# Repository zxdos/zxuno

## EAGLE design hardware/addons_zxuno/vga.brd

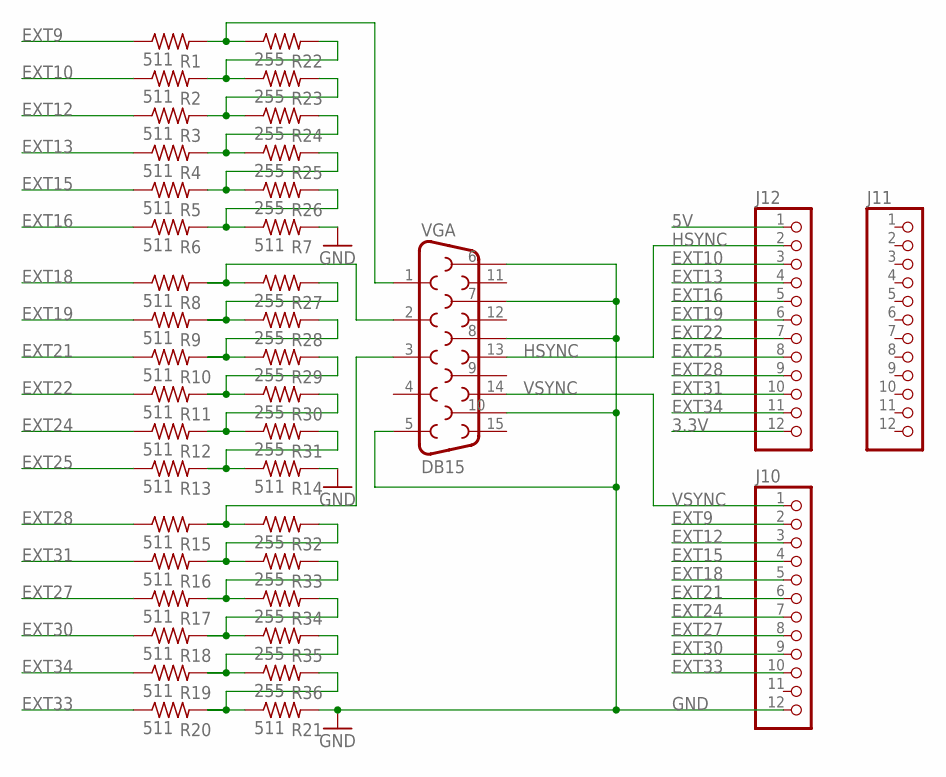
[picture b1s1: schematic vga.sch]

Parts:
J10, J11, J12: PINHD-1X12; 1X12
R1, R2, R3, R4, R5, R6, R7, R8, R9, R10, R11, R12, R13, R14, R15, R16, R17, R18, R19, R20, R21: 511; R0805
R22, R23, R24, R25, R26, R27, R28, R29, R30, R31, R32, R33, R34, R35, R36: 255; R0805
VGA: DB15

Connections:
3.3V: J12.12
5V: J12.1
EXT9: J10.2, R1.1
EXT10: J12.3, R2.1
EXT12: J10.3, R3.1
EXT13: J12.4, R4.1
EXT15: J10.4, R5.1
EXT16: J12.5, R6.1
EXT18: J10.5, R8.1
EXT19: J12.6, R9.1
EXT21: J10.6, R10.1
EXT22: J12.7, R11.1
EXT24: J10.7, R12.1
EXT25: J12.8, R13.1
EXT27: J10.8, R17.1
EXT28: J12.9, R15.1
EXT30: J10.9, R18.1
EXT31: J12.10, R16.1
EXT33: J10.10, R20.1
EXT34: J12.11, R19.1
GND: J10.12, R7.2, R14.2, R21.2, VGA.5, VGA.6, VGA.7, VGA.8, VGA.10
GREEN: R8.2, R27.1, VGA.2
HSYNC: J12.2, VGA.13
unnamed: R20.2, R21.1, R36.2
unnamed: R9.2, R27.2, R28.1
unnamed: R2.2, R22.2, R23.1
unnamed: R1.2, R22.1, VGA.1
unnamed: R12.2, R30.2, R31.1
unnamed: R6.2, R7.1, R26.2
unnamed: R3.2, R23.2, R24.1
unnamed: R4.2, R24.2, R25.1
unnamed: R5.2, R25.2, R26.1
unnamed: R11.2, R29.2, R30.1
unnamed: R13.2, R14.1, R31.2
unnamed: R10.2, R28.2, R29.1
unnamed: R15.2, R32.1, VGA.3
unnamed: R16.2, R32.2, R33.1
unnamed: R17.2, R33.2, R34.1
unnamed: R18.2, R34.2, R35.1
unnamed: R19.2, R35.2, R36.1
VSYNC: J10.1, VGA.14

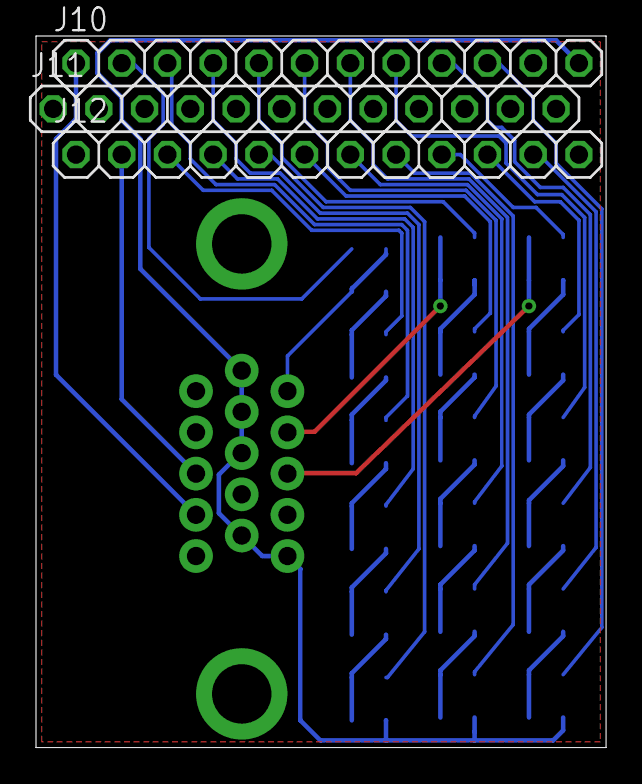
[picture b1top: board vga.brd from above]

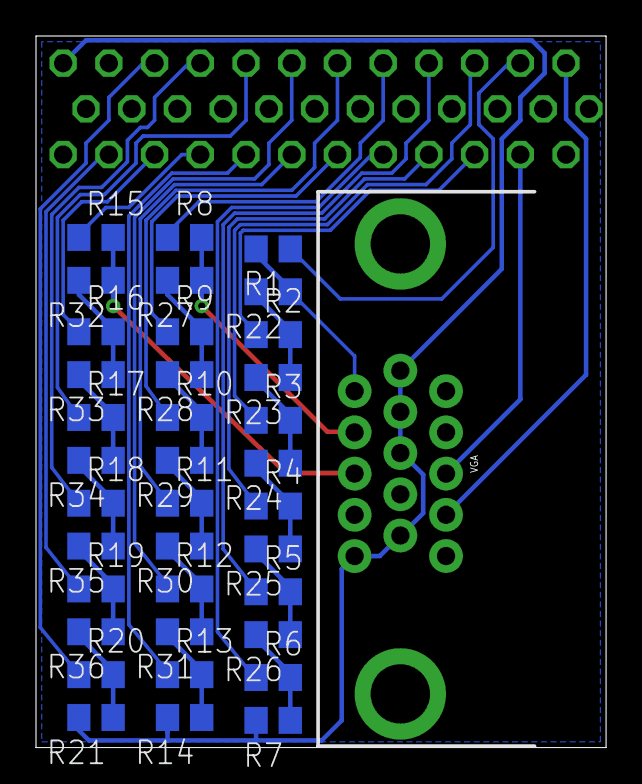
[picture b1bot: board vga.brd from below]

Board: 2 copper layers, 31.7 x 39.5 mm, 40 parts (37 on the bottom side), 39 nets.

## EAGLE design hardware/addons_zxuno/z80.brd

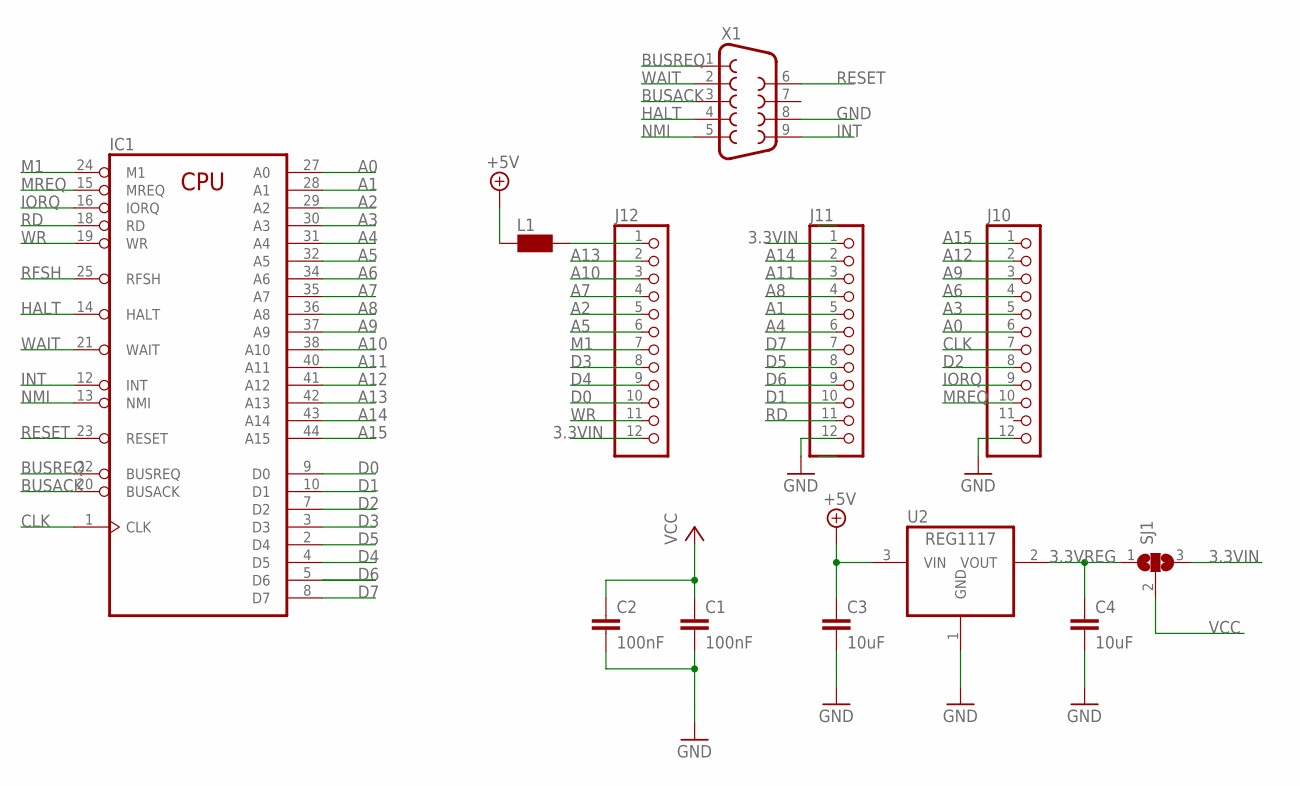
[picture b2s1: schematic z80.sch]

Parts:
C1, C2: 100nF; C0805K
C3, C4: 10uF; C0805K
IC1: Z80CPU-F; QFP-44
J10, J11, J12: PINHD-1X12; 1X12
L1: WE-CBF_0805; 0805
SJ1: SJ2W; SJ_2
U2: REG1117; SOT223
X1: F09D

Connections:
3.3VIN: J11.1, J12.12, SJ1.3
3.3VREG: C4.1, SJ1.1, U2.2 (VOUT)
+5V: C3.1, L1.2, U2.3 (VIN)
A0: IC1.27 (A0), J10.6
A1: IC1.28 (A1), J11.5
A2: IC1.29 (A2), J12.5
A3: IC1.30 (A3), J10.5
A4: IC1.31 (A4), J11.6
A5: IC1.32 (A5), J12.6
A6: IC1.34 (A6), J10.4
A7: IC1.35 (A7), J12.4
A8: IC1.36 (A8), J11.4
A9: IC1.37 (A9), J10.3
A10: IC1.38 (A10), J12.3
A11: IC1.40 (A11), J11.3
A12: IC1.41 (A12), J10.2
A13: IC1.42 (A13), J12.2
A14: IC1.43 (A14), J11.2
A15: IC1.44 (A15), J10.1
BUSACK: IC1.20 (BUSACK), X1.3
BUSREQ: IC1.22 (BUSREQ), X1.1
CLK: IC1.1 (CLK), J10.7
D0: IC1.9 (D0), J12.10
D1: IC1.10 (D1), J11.10
D2: IC1.7 (D2), J10.8
D3: IC1.3 (D3), J12.8
D4: IC1.4 (D5), J12.9
D5: IC1.2 (D4), J11.8
D6: IC1.5 (D6), J11.9
D7: IC1.8 (D7), J11.7
GND: C1.2, C2.2, C3.2, C4.2, IC1.26 (GND), J10.12, J11.12, U2.1 (GND), X1.8
HALT: IC1.14 (HALT), X1.4
INT: IC1.12 (INT), X1.9
IORQ: IC1.16 (IORQ), J10.9
M1: IC1.24 (M1), J12.7
MREQ: IC1.15 (MREQ), J10.10
unnamed: J12.1, L1.1
NMI: IC1.13 (NMI), X1.5
RD: IC1.18 (RD), J11.11
RESET: IC1.23 (RESET), X1.6
RFSH: IC1.25 (RFSH)
VCC: C1.1, C2.1, IC1.6 (VCC), SJ1.2
WAIT: IC1.21 (WAIT), X1.2
WR: IC1.19 (WR), J12.11

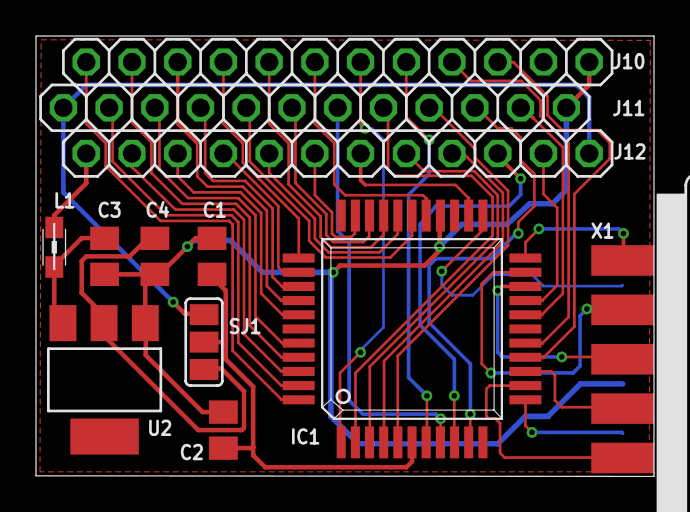
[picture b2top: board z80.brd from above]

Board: 2 copper layers, 34.3 x 24.5 mm, 12 parts (0 on the bottom side), 43 nets.

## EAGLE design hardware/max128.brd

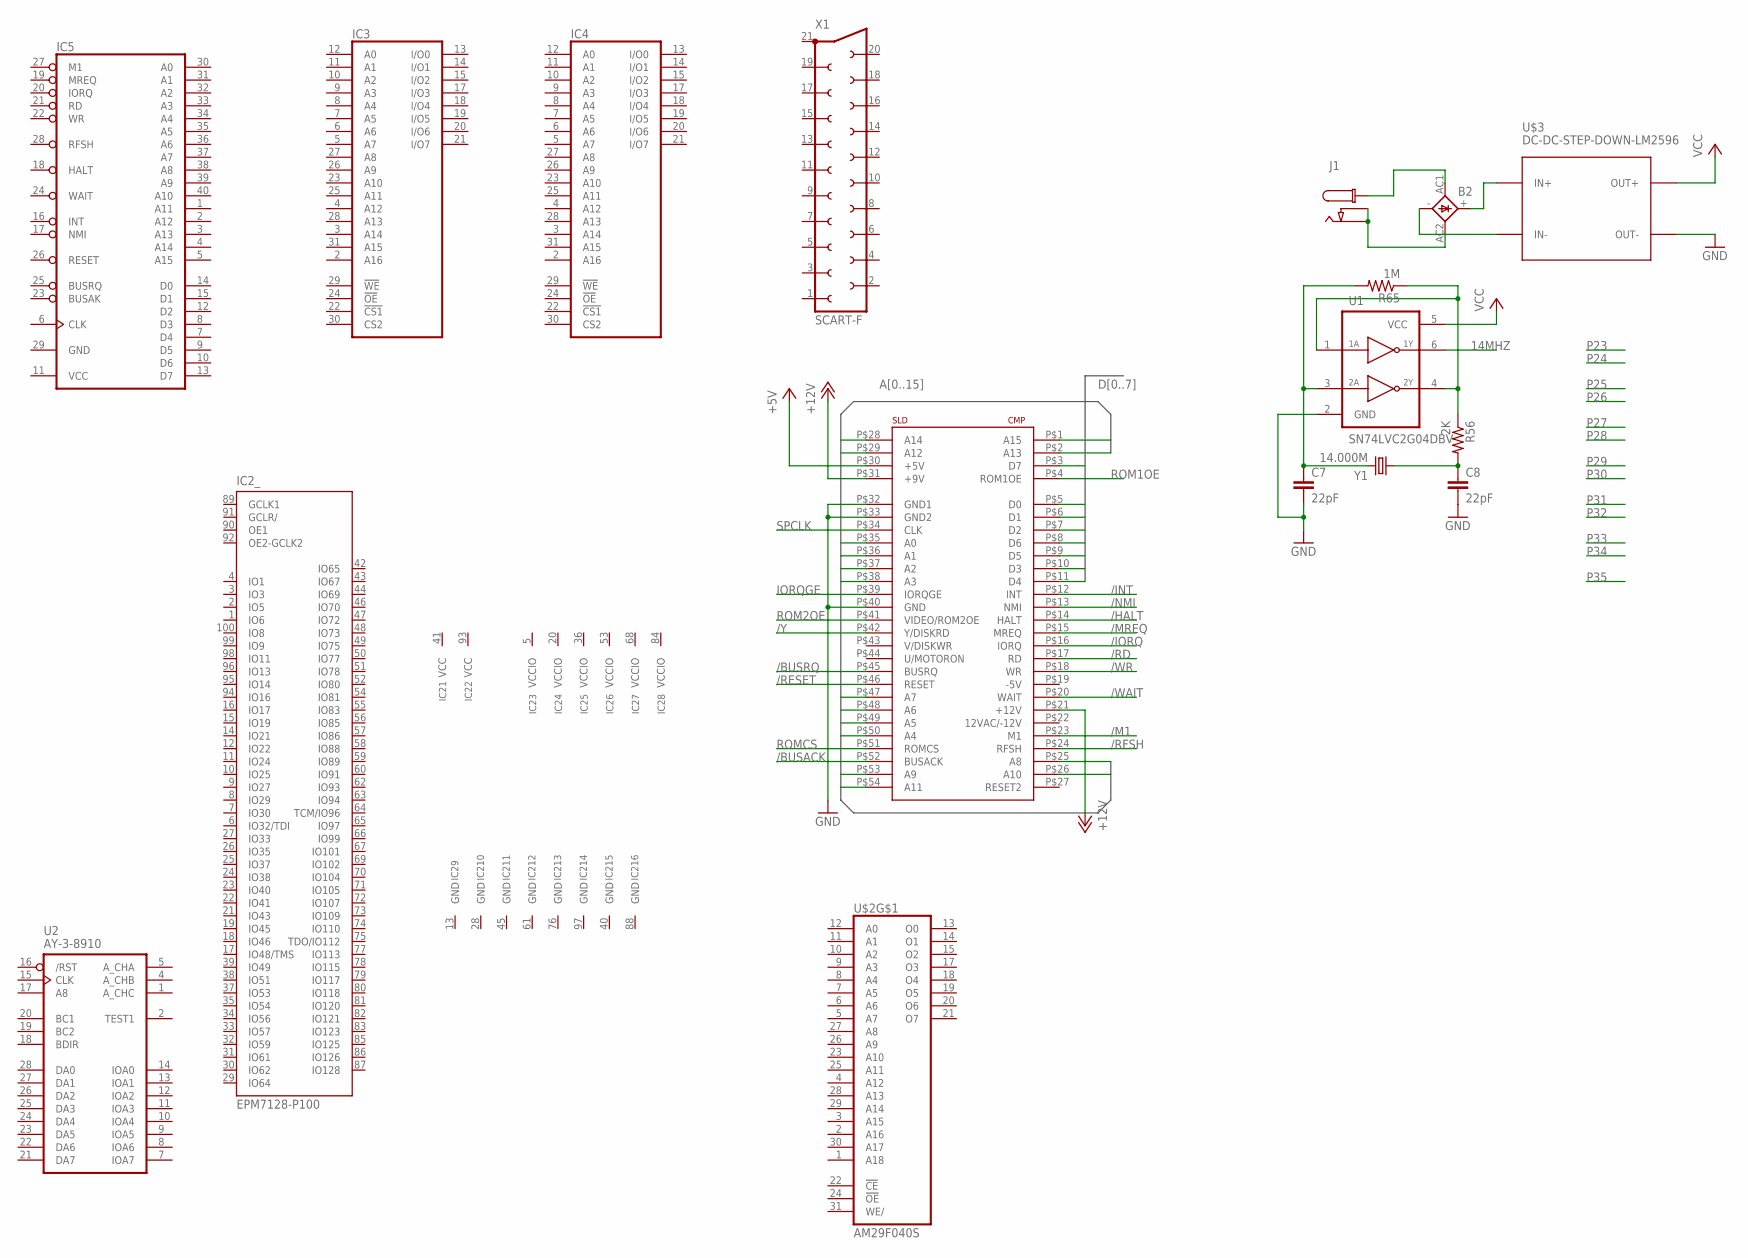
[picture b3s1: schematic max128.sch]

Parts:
B2: 1KAB
C7, C8: 22pF; C0805K
IC2: EPM7128-P100; PQFP100
IC3, IC4: LP621024CM; SOP32L
IC5: Z80CPU; DIL40
J1: CON_DC_M-DC_PTH2; DC_BARREL_JACK_PTH_2MM_2
R56: 2K; R0805
R65: 1M; R0805
U1: SN74LVC2G04DBV; SOT23-6
U2: AY-3-8910; DIL28-6
U$1: CONECTOR_EDGE_LADO_SPECTRUM; CONECTOR_LADO_SPECTRUM
U$2: AM29F040S; PLCC-SR32
U$3: DC-DC-STEP-DOWN-LM2596
X1: SCART-F
Y1: 14.000M; HC49/S

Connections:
14MHZ: U1.6 (1Y)
+5V: U$1.P$30 (+5V)
+12V: U$1.P$21 (+12V), U$1.P$31 (+9V)
/BUSACK: U$1.P$52 (BUSACK)
/BUSRQ: U$1.P$45 (BUSRQ)
/HALT: U$1.P$14 (HALT)
/INT: U$1.P$12 (INT)
/IORQ: U$1.P$16 (IORQ)
/M1: U$1.P$23 (M1)
/MREQ: U$1.P$15 (MREQ)
/NMI: U$1.P$13 (NMI)
/RD: U$1.P$17 (RD)
/RESET: U$1.P$46 (RESET)
/RFSH: U$1.P$24 (RFSH)
/WAIT: U$1.P$20 (WAIT)
/WR: U$1.P$18 (WR)
/Y: U$1.P$42 (Y/DISKRD)
A0: U$1.P$35 (A0)
A1: U$1.P$36 (A1)
A2: U$1.P$37 (A2)
A3: U$1.P$38 (A3)
A4: U$1.P$50 (A4)
A5: U$1.P$49 (A5)
A6: U$1.P$48 (A6)
A7: U$1.P$47 (A7)
A8: U$1.P$25 (A8)
A9: U$1.P$53 (A9)
A10: U$1.P$26 (A10)
A11: U$1.P$54 (A11)
A12: U$1.P$29 (A12)
A13: U$1.P$2 (A13)
A14: U$1.P$28 (A14)
A15: U$1.P$1 (A15)
D0: U$1.P$5 (D0)
D1: U$1.P$6 (D1)
D2: U$1.P$7 (D2)
D3: U$1.P$10 (D3)
D4: U$1.P$11 (D4)
D5: U$1.P$9 (D5)
D6: U$1.P$8 (D6)
D7: U$1.P$3 (D7)
GND: C7.2, C8.2, IC2.13 (GND), IC2.28 (GND), IC2.40 (GND), IC2.45 (GND), IC2.61 (GND), IC2.76 (GND), IC2.88 (GND), IC2.97 (GND), IC3.16 (GND), IC4.16 (GND), IC5.29 (GND), U1.2 (GND), U2.6 (GND), U$1.P$32 (GND1), U$1.P$33 (GND2), U$1.P$40 (GND), U$2.16 (GND), U$3.OUT-
IORQGE: U$1.P$39 (IORQGE)
unnamed: B2.AC1, J1.P1
unnamed: B2.AC2, J1.P2 (P3), J1.P3 (P2)
unnamed: B2.+, U$3.IN+
unnamed: B2.-, U$3.IN-
unnamed: C7.1, R65.2, U1.3 (2A), Y1.2
unnamed: R56.1, R65.1, U1.1 (1A), U1.4 (2Y)
unnamed: C8.1, R56.2, Y1.1
ROM1OE: U$1.P$4 (ROM1OE)
ROM2OE: U$1.P$41 (VIDEO/ROM2OE)
ROMCS: U$1.P$51 (ROMCS)
SPCLK: U$1.P$34 (CLK)
VCC: IC2.41 (VCC), IC2.93 (VCC), IC3.32 (VCC), IC4.32 (VCC), IC5.11 (VCC), U1.5 (VCC), U2.3 (VCC), U$2.32 (VCC), U$3.OUT+
VCCIO: IC2.5 (VCCIO), IC2.20 (VCCIO), IC2.36 (VCCIO), IC2.53 (VCCIO), IC2.68 (VCCIO), IC2.84 (VCCIO)

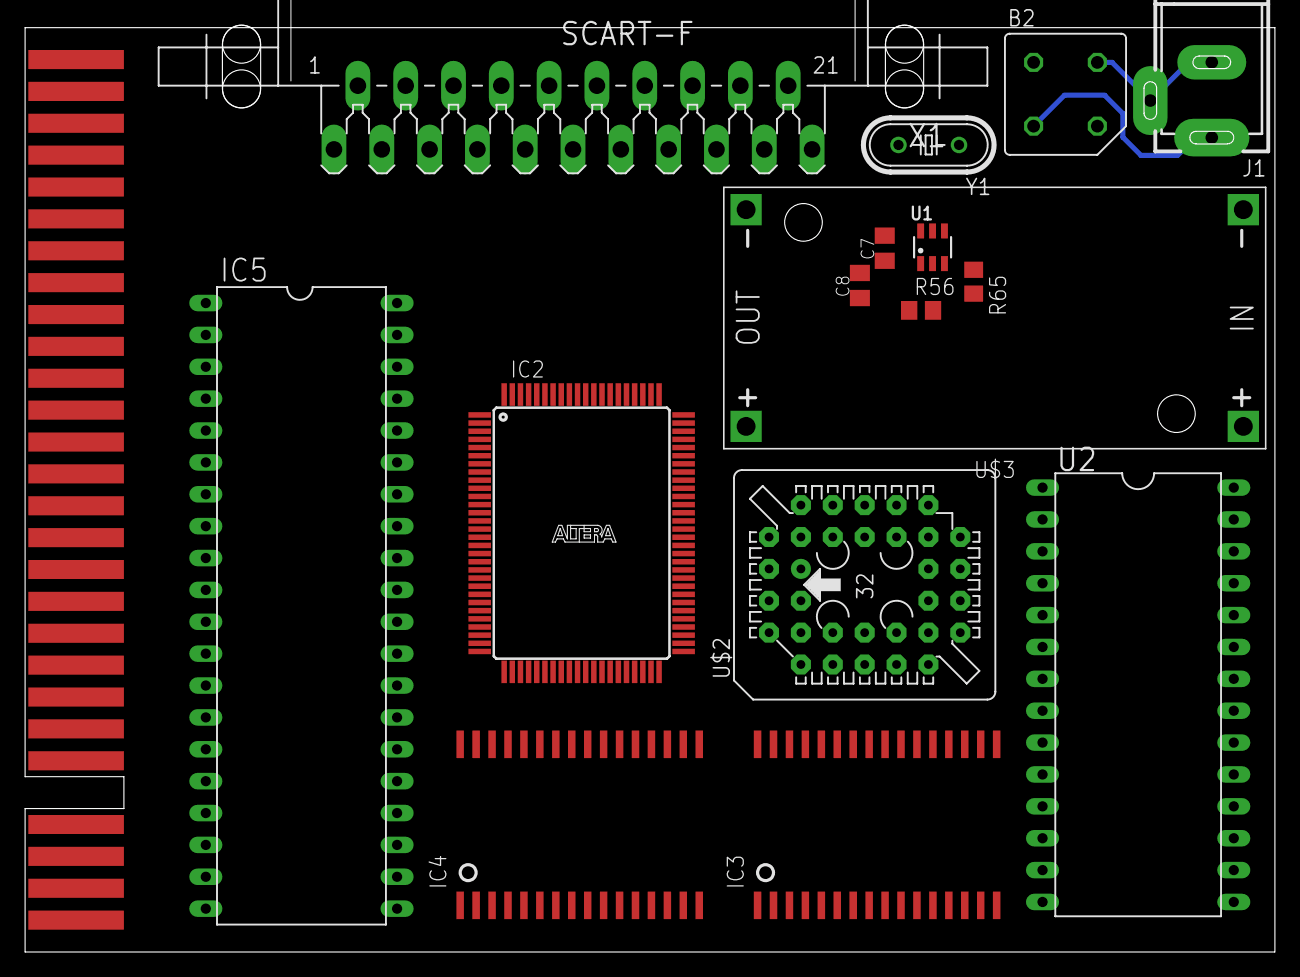
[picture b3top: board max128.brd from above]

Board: 2 copper layers, 99.6 x 73.7 mm, 17 parts (0 on the bottom side), 11 nets.

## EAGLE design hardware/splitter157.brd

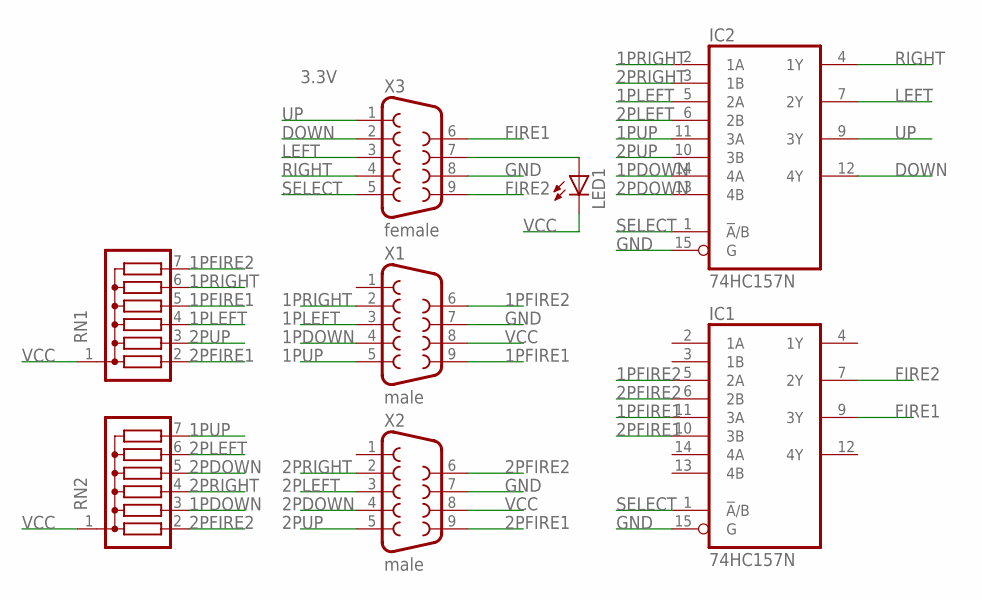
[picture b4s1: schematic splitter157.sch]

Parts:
IC1, IC2: 74HC157N; DIL16NUEVO
LED1: LED3MM
RN1, RN2: G06R; SIL7
X1, X2: male; F09D
X3: female; F09D

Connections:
1PDOWN: IC2.14 (4A), RN2.3, X1.4
1PFIRE1: IC1.11 (3A), RN1.5, X1.9
1PFIRE2: IC1.5 (2A), RN1.7, X1.6
1PLEFT: IC2.5 (2A), RN1.4, X1.3
1PRIGHT: IC2.2 (1A), RN1.6, X1.2
1PUP: IC2.11 (3A), RN2.7, X1.5
2PDOWN: IC2.13 (4B), RN2.5, X2.4
2PFIRE1: IC1.10 (3B), RN1.2, X2.9
2PFIRE2: IC1.6 (2B), RN2.2, X2.6
2PLEFT: IC2.6 (2B), RN2.6, X2.3
2PRIGHT: IC2.3 (1B), RN2.4, X2.2
2PUP: IC2.10 (3B), RN1.3, X2.5
DOWN: IC2.12 (4Y), X3.2
FIRE1: IC1.9 (3Y), X3.6
FIRE2: IC1.7 (2Y), X3.9
GND: IC1.8 (GND), IC1.15 (G), IC2.8 (GND), IC2.15 (G), X1.7, X2.7, X3.8
LEFT: IC2.7 (2Y), X3.3
unnamed: LED1.A, X3.7
RIGHT: IC2.4 (1Y), X3.4
SELECT: IC1.1 (!A!/B), IC2.1 (!A!/B), X3.5
UP: IC2.9 (3Y), X3.1
VCC: IC1.16 (VCC), IC2.16 (VCC), LED1.K (C), RN1.1, RN2.1, X1.8, X2.8

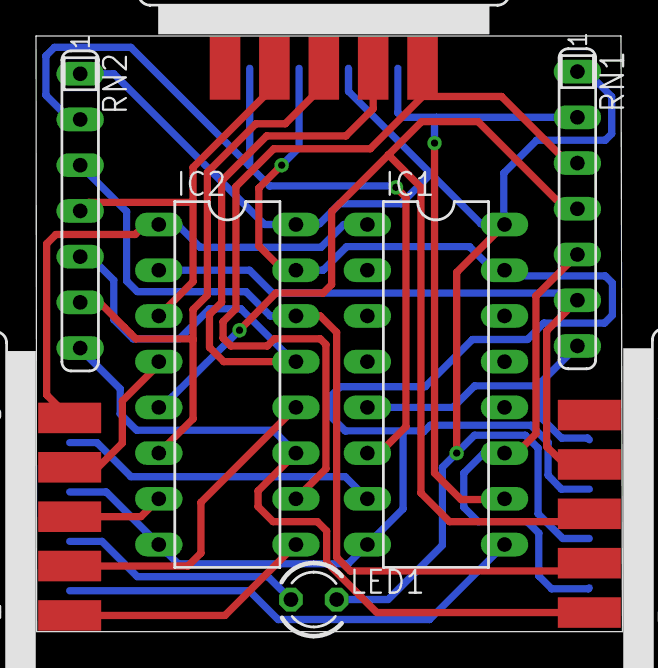
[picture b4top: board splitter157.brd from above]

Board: 2 copper layers, 32.6 x 33.1 mm, 8 parts (0 on the bottom side), 22 nets.

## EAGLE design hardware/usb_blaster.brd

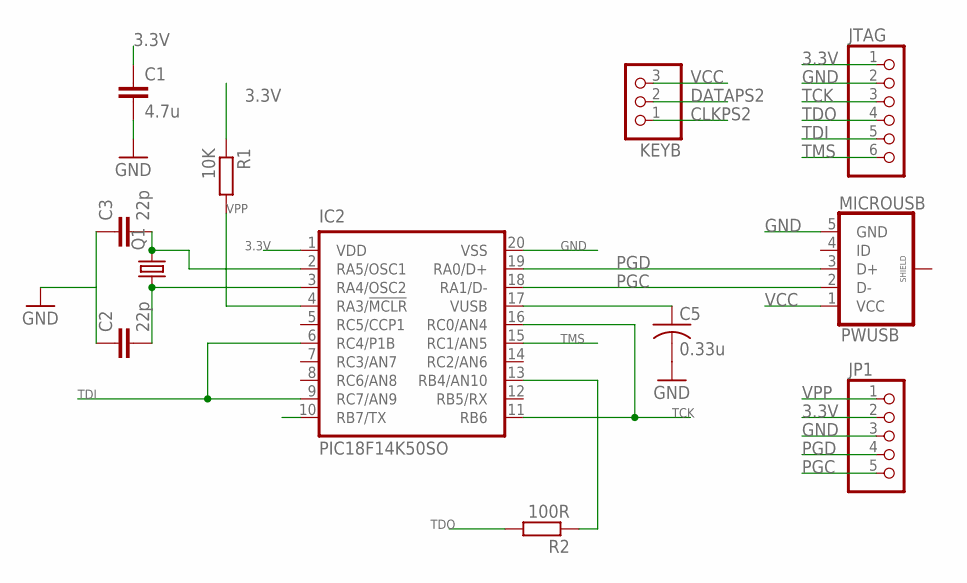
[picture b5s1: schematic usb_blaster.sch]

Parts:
C1: 4.7u; C0805
C2, C3: 22p; C0805
C5: 0.33u; C0805
IC2: PIC18F14K50SO; SO20
JP1: PINHD-1X5; 1X05
JTAG: PINHD-1X6; 1X06
KEYB: PINHD-1X3; 1X03
PWUSB: MICROUSB; MICRO_USB_1PRIMARY
Q1: CRYSTALHC49UP; HC49UP
R1: 10K; R0805
R2: 100R; R0805

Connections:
3.3V: C1.1, IC2.1 (VDD), JP1.2, JTAG.1, R1.1
CLKPS2: KEYB.1
DATAPS2: KEYB.2
GND: C1.2, C2.1, C3.1, C5.2, IC2.20 (VSS), JP1.3, JTAG.2, PWUSB.5 (GND)
unnamed: C3.2, IC2.2 (RA5/OSC1), Q1.2
unnamed: C2.2, IC2.3 (RA4/OSC2), Q1.1
unnamed: IC2.13 (RB4/AN10), R2.1
unnamed: C5.1, IC2.17 (VUSB)
PGC: IC2.18 (RA1/D-), JP1.5, PWUSB.2 (D-)
PGD: IC2.19 (RA0/D+), JP1.4, PWUSB.3 (D+)
TCK: IC2.11 (RB6), IC2.16 (RC0/AN4), JTAG.3
TDI: IC2.6 (RC4/P1B), IC2.9 (RC7/AN9), JTAG.5
TDO: JTAG.4, R2.2
TMS: IC2.15 (RC1/AN5), JTAG.6
VCC: KEYB.3, PWUSB.1 (VCC)
VPP: IC2.4 (RA3/!MCLR!), JP1.1, R1.2

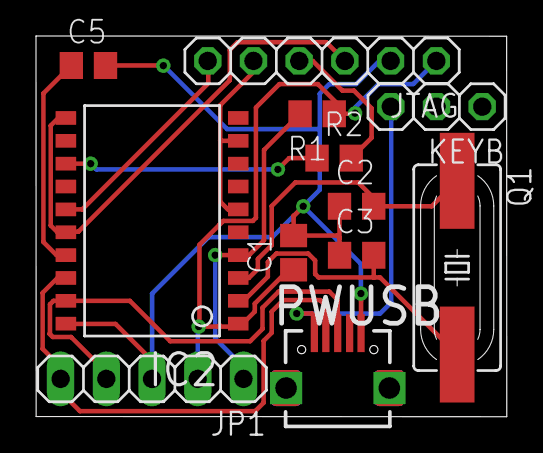
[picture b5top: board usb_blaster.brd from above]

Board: 2 copper layers, 26.2 x 21.2 mm, 12 parts (0 on the bottom side), 14 nets.

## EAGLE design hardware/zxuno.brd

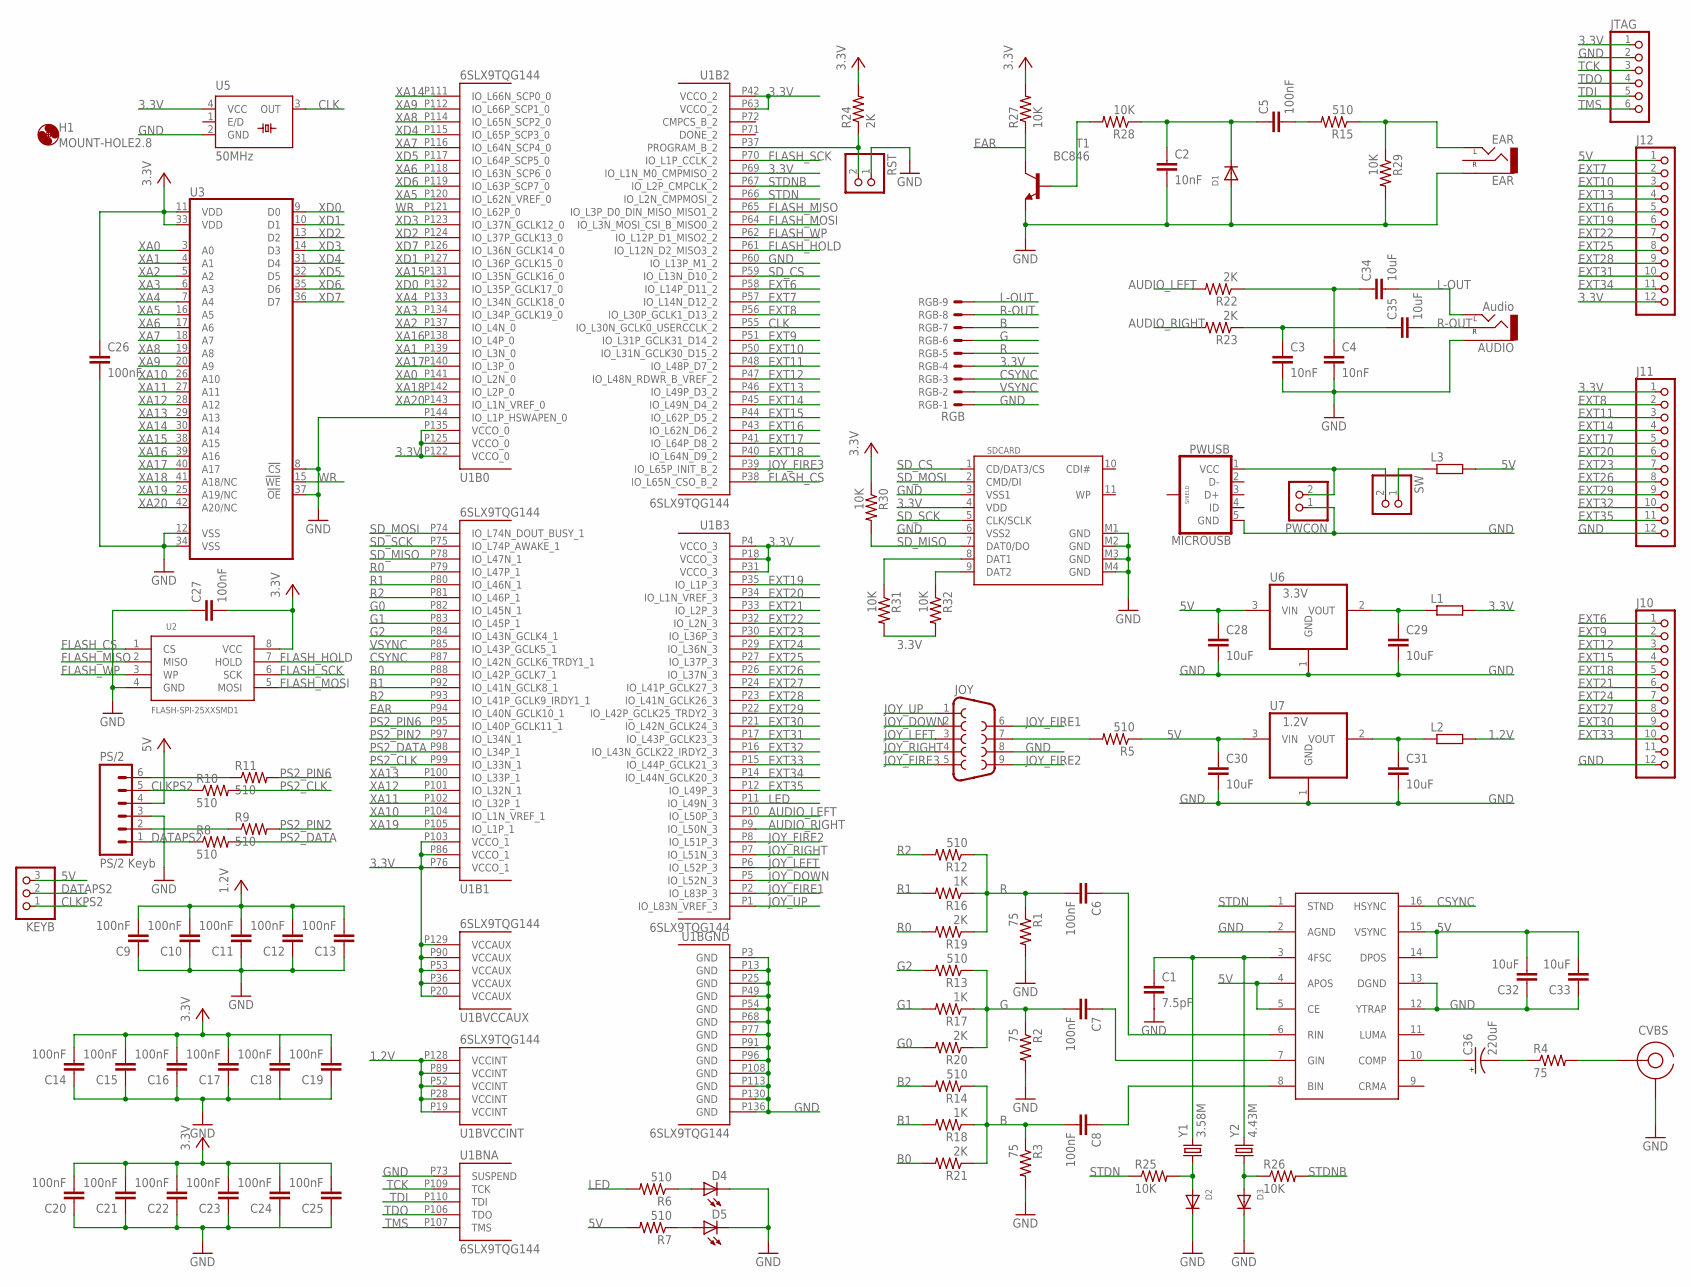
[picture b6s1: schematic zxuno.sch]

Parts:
AUDIO: Audio; AUDIO-JACK
C1: 7.5pF; C0805
C2, C3, C4: 10nF; C0805
C5, C6, C7, C8, C9, C10, C11, C12, C13, C14, C15, C16, C17, C18, C19, C20, C21, C22, C23, C24, C25, C26, C27: 100nF; C0603
C28, C29, C30, C31, C32, C33, C34, C35: 10uF; C0805
C36: 220uF; 153CLV-0605
CVBS: RCA
D1, D2, D3: DIODESOD-323F; SOD-323F
D4, D5: LEDCHIP-LED0805; CHIP-LED0805
EAR: EAR; AUDIO-JACK
H1: MOUNT-HOLE2.8; 2,8
J10, J11, J12: PINHD-1X12; 1X12
JOY: DB9MALE; DB9_MALE
JTAG: PINHD-1X6; 1X06
KEYB: PINHD-1X3; 1X03
L1, L2, L3: R-EU_M0805; M0805
PS/2: PS/2 Keyb; DINC/MIN_TM/6_1PRIMARY
PWCON: PINHD-1X2; 1X02
PWUSB: MICROUSB; MICRO_USB_1PRIMARY
R1, R2, R3, R4: 75; M0805
R5, R6, R7, R8, R9, R10, R11, R12, R13, R14, R15: 510; M0805
R16, R17, R18: 1K; M0805
R19, R20, R21, R22, R23, R24: 2K; M0805
R25, R26, R27, R28, R29, R30, R31, R32: 10K; M0805
RGB: RGB; 53048-09
RST: PINHD-1X2; 1X02
SDCARD: SDCARD; SDCMF-10915W010
SW: PINHD-1X2; 1X02
T1: BC846; SOT23
U1: 6SLX9TQG144; TQ144
U2: FLASH-SPI-25XXSMD1; SO08-EIAJ
U3: ISSI_SRAM_8BIT; TSOP44-II
U4: AD724; SO16W
U5: 50MHz; SM/OSC_1PRIMARY
U6: 3.3V; SOT223
U7: 1.2V; SOT223
Y1: 3.58M; HC49UP
Y2: 4.43M; HC49UP

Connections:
1.2V: C9.2, C10.2, C11.2, C12.2, C13.2, L2.2, U1.P19 (VCCINT), U1.P28 (VCCINT), U1.P52 (VCCINT), U1.P89 (VCCINT), U1.P128 (VCCINT)
3.3V: C14.2, C15.2, C16.2, C17.2, C18.2, C19.2, C20.2, C21.2, C22.2, C23.2, C24.2, C25.2, C26.1, C27.2, J11.1, J12.12, JTAG.1, L1.2, R24.2, R27.2, R30.1, R31.2, R32.2, RGB.4, SDCARD.4 (VDD), U1.P4 (VCCO_3), U1.P18 (VCCO_3), U1.P20 (VCCAUX), U1.P31 (VCCO_3), U1.P36 (VCCAUX), U1.P42 (VCCO_2), U1.P53 (VCCAUX), U1.P63 (VCCO_2), U1.P69 (IO_L1N_M0_CMPMISO_2), U1.P76 (VCCO_1), U1.P86 (VCCO_1), U1.P90 (VCCAUX), U1.P103 (VCCO_1), U1.P122 (VCCO_0), U1.P125 (VCCO_0), U1.P129 (VCCAUX), U1.P135 (VCCO_0), U2.8 (VCC), U3.11 (VDD), U3.33 (VDD), U5.4 (VCC)
5V: C28.1, C30.1, C32.2, C33.2, J12.1, KEYB.3, L3.2, PS/2.4, R5.1, R7.2, U4.4 (APOS), U4.5 (CE), U4.14 (DPOS), U4.15 (VSYNC), U6.3 (VIN), U7.3 (VIN)
AUDIO_LEFT: R22.2, U1.P10 (IO_L50P_3)
AUDIO_RIGHT: R23.2, U1.P9 (IO_L50N_3)
B: C8.2, R3.1, R14.1, R18.1, R21.1, RGB.7
B0: R21.2, U1.P88 (IO_L42P_GCLK7_1)
B1: R18.2, U1.P92 (IO_L41N_GCLK8_1)
B2: R14.2, U1.P93 (IO_L41P_GCLK9_IRDY1_1)
CLK: U1.P55 (IO_L30N_GCLK0_USERCCLK_2), U5.3 (OUT)
CLKPS2: KEYB.1, PS/2.5, R10.1
CSYNC: RGB.3, U1.P87 (IO_L42N_GCLK6_TRDY1_1), U4.16 (HSYNC)
DATAPS2: KEYB.2, PS/2.1, R8.1
EAR: R27.1, T1.3 (C), U1.P94 (IO_L40N_GCLK10_1)
EXT6: J10.1, U1.P58 (IO_L14P_D11_2)
EXT7: J12.2, U1.P57 (IO_L14N_D12_2)
EXT8: J11.2, U1.P56 (IO_L30P_GCLK1_D13_2)
EXT9: J10.2, U1.P51 (IO_L31P_GCLK31_D14_2)
EXT10: J12.3, U1.P50 (IO_L31N_GCLK30_D15_2)
EXT11: J11.3, U1.P48 (IO_L48P_D7_2)
EXT12: J10.3, U1.P47 (IO_L48N_RDWR_B_VREF_2)
EXT13: J12.4, U1.P46 (IO_L49P_D3_2)
EXT14: J11.4, U1.P45 (IO_L49N_D4_2)
EXT15: J10.4, U1.P44 (IO_L62P_D5_2)
EXT16: J12.5, U1.P43 (IO_L62N_D6_2)
EXT17: J11.5, U1.P41 (IO_L64P_D8_2)
EXT18: J10.5, U1.P40 (IO_L64N_D9_2)
EXT19: J12.6, U1.P35 (IO_L1P_3)
EXT20: J11.6, U1.P34 (IO_L1N_VREF_3)
EXT21: J10.6, U1.P33 (IO_L2P_3)
EXT22: J12.7, U1.P32 (IO_L2N_3)
EXT23: J11.7, U1.P30 (IO_L36P_3)
EXT24: J10.7, U1.P29 (IO_L36N_3)
EXT25: J12.8, U1.P27 (IO_L37P_3)
EXT26: J11.8, U1.P26 (IO_L37N_3)
EXT27: J10.8, U1.P24 (IO_L41P_GCLK27_3)
EXT28: J12.9, U1.P23 (IO_L41N_GCLK26_3)
EXT29: J11.9, U1.P22 (IO_L42P_GCLK25_TRDY2_3)
EXT30: J10.9, U1.P21 (IO_L42N_GCLK24_3)
EXT31: J12.10, U1.P17 (IO_L43P_GCLK23_3)
EXT32: J11.10, U1.P16 (IO_L43N_GCLK22_IRDY2_3)
EXT33: J10.10, U1.P15 (IO_L44P_GCLK21_3)
EXT34: J12.11, U1.P14 (IO_L44N_GCLK20_3)
EXT35: J11.11, U1.P12 (IO_L49P_3)
FLASH_CS: U1.P38 (IO_L65N_CSO_B_2), U2.1 (CS)
FLASH_HOLD: U1.P61 (IO_L12N_D2_MISO3_2), U2.7 (HOLD)
FLASH_MISO: U1.P65 (IO_L3P_D0_DIN_MISO_MISO1_2), U2.2 (MISO)
FLASH_MOSI: U1.P64 (IO_L3N_MOSI_CSI_B_MISO0_2), U2.5 (MOSI)
FLASH_SCK: U1.P70 (IO_L1P_CCLK_2), U2.6 (SCK)
FLASH_WP: U1.P62 (IO_L12P_D1_MISO2_2), U2.3 (WP)
G: C7.2, R2.1, R13.1, R17.1, R20.1, RGB.6
G0: R20.2, U1.P82 (IO_L45N_1)
G1: R17.2, U1.P83 (IO_L45P_1)
G2: R13.2, U1.P84 (IO_L43N_GCLK4_1)
GND: AUDIO.SLEEVE, C1.2, C2.2, C3.2, C4.2, C9.1, C10.1, C11.1, C12.1, C13.1, C14.1, C15.1, C16.1, C17.1, C18.1, C19.1, C20.1, C21.1, C22.1, C23.1, C24.1, C25.1, C26.2, C27.1, C28.2, C29.2, C30.2, C31.2, C32.1, C33.1, CVBS.GND, D1.A, D2.C, D3.C, D4.C, D5.C, EAR.SLEEVE, J10.12, J11.12, JOY.8, JTAG.2, PS/2.3, PWCON.1, PWUSB.5 (GND), R1.2, R2.2, R3.2, R29.2, RGB.1, RST.1, SDCARD.3 (VSS1), SDCARD.6 (VSS2), SDCARD.M1 (GND), SDCARD.M2 (GND), SDCARD.M3 (GND), SDCARD.M4 (GND), T1.2 (E), U1.P3 (GND), U1.P13 (GND), U1.P25 (GND), U1.P49 (GND), U1.P54 (GND), U1.P60 (IO_L13P_M1_2), U1.P68 (GND), U1.P73 (SUSPEND), U1.P77 (GND), U1.P91 (GND), U1.P96 (GND), U1.P108 (GND), U1.P113 (GND), U1.P130 (GND), U1.P136 (GND), U1.P144 (IO_L1P_HSWAPEN_0), U2.4 (GND), U3.8 (!CS), U3.12 (VSS), U3.34 (VSS), U3.37 (!OE), U4.2 (AGND), U4.12 (YTRAP), U4.13 (DGND), U5.2 (GND), U6.1 (GND), U7.1 (GND)
JOY_DOWN: JOY.2, U1.P5 (IO_L52N_3)
JOY_FIRE1: JOY.6, U1.P2 (IO_L83P_3)
JOY_FIRE2: JOY.9, U1.P8 (IO_L51P_3)
JOY_FIRE3: JOY.5, U1.P39 (IO_L65P_INIT_B_2)
JOY_LEFT: JOY.3, U1.P6 (IO_L52P_3)
JOY_RIGHT: JOY.4, U1.P7 (IO_L51N_3)
JOY_UP: JOY.1, U1.P1 (IO_L83N_VREF_3)
L-OUT: AUDIO.TIP (LEFT), C34.2, RGB.9
LED: R6.2, U1.P11 (IO_L49N_3)
unnamed: PS/2.6, R11.1
unnamed: PS/2.2, R9.1
unnamed: R24.1, RST.2, U1.P37 (PROGRAM_B_2)
unnamed: R28.2, T1.1 (B)
unnamed: C2.1, C5.1, D1.C, R28.1
unnamed: C5.2, R15.2
unnamed: EAR.TIP (LEFT), R15.1, R29.1
unnamed: C3.1, C35.1, R23.1
unnamed: C4.1, C34.1, R22.1
unnamed: PWCON.2, PWUSB.1 (VCC), SW.2
unnamed: L3.1, SW.1
unnamed: C29.1, L1.1, U6.2 (VOUT)
unnamed: JOY.7, R5.2
unnamed: C31.1, L2.1, U7.2 (VOUT)
unnamed: R31.1, SDCARD.8 (DAT1)
unnamed: C8.1, U4.8 (BIN)
unnamed: R32.1, SDCARD.9 (DAT2)
unnamed: C7.1, U4.7 (GIN)
unnamed: C6.1, U4.6 (RIN)
unnamed: C1.1, U4.3 (4FSC), Y1.2, Y2.2
unnamed: D3.A, R26.1, Y2.1
unnamed: D2.A, R25.2, Y1.1
unnamed: C36.+, U4.10 (COMP)
unnamed: C36.-, R4.1
unnamed: CVBS.SIG, R4.2
unnamed: D4.A, R6.1
unnamed: D5.A, R7.1
PS2_CLK: R10.2, U1.P99 (IO_L33N_1)
PS2_DATA: R8.2, U1.P98 (IO_L34P_1)
PS2_PIN2: R9.2, U1.P97 (IO_L34N_1)
PS2_PIN6: R11.2, U1.P95 (IO_L40P_GCLK11_1)
R: C6.2, R1.1, R12.1, R16.1, R19.1, RGB.5
R0: R19.2, U1.P79 (IO_L47P_1)
R1: R16.2, U1.P80 (IO_L46N_1)
R2: R12.2, U1.P81 (IO_L46P_1)
R-OUT: AUDIO.RING (RIGHT), C35.2, RGB.8
SD_CS: SDCARD.1 (CD/DAT3/CS), U1.P59 (IO_L13N_D10_2)
SD_MISO: R30.2, SDCARD.7 (DAT0/DO), U1.P78 (IO_L47N_1)
SD_MOSI: SDCARD.2 (CMD/DI), U1.P74 (IO_L74N_DOUT_BUSY_1)
SD_SCK: SDCARD.5 (CLK/SCLK), U1.P75 (IO_L74P_AWAKE_1)
STDN: R25.1, U1.P66 (IO_L2N_CMPMOSI_2), U4.1 (STND)
STDNB: R26.2, U1.P67 (IO_L2P_CMPCLK_2)
TCK: JTAG.3, U1.P109 (TCK)
TDI: JTAG.5, U1.P110 (TDI)
TDO: JTAG.4, U1.P106 (TDO)
TMS: JTAG.6, U1.P107 (TMS)
VSYNC: RGB.2, U1.P85 (IO_L43P_GCLK5_1)
WR: U1.P121 (IO_L62P_0), U3.15 (!WE)
XA0: U1.P141 (IO_L2N_0), U3.3 (A0)
XA1: U1.P139 (IO_L3N_0), U3.4 (A1)
XA2: U1.P137 (IO_L4N_0), U3.5 (A2)
XA3: U1.P134 (IO_L34P_GCLK19_0), U3.6 (A3)
XA4: U1.P133 (IO_L34N_GCLK18_0), U3.7 (A4)
XA5: U1.P120 (IO_L62N_VREF_0), U3.16 (A5)
XA6: U1.P118 (IO_L63N_SCP6_0), U3.17 (A6)
XA7: U1.P116 (IO_L64N_SCP4_0), U3.18 (A7)
XA8: U1.P114 (IO_L65N_SCP2_0), U3.19 (A8)
XA9: U1.P112 (IO_L66P_SCP1_0), U3.20 (A9)
XA10: U1.P104 (IO_L1N_VREF_1), U3.26 (A10)
XA11: U1.P102 (IO_L32P_1), U3.27 (A11)
XA12: U1.P101 (IO_L32N_1), U3.28 (A12)
XA13: U1.P100 (IO_L33P_1), U3.29 (A13)
XA14: U1.P111 (IO_L66N_SCP0_0), U3.30 (A14)
XA15: U1.P131 (IO_L35N_GCLK16_0), U3.38 (A15)
XA16: U1.P138 (IO_L4P_0), U3.39 (A16)
XA17: U1.P140 (IO_L3P_0), U3.40 (A17)
XA18: U1.P142 (IO_L2P_0), U3.41 (A18/NC)
XA19: U1.P105 (IO_L1P_1), U3.25 (A19/NC)
XA20: U1.P143 (IO_L1N_VREF_0), U3.42 (A20/NC)
XD0: U1.P132 (IO_L35P_GCLK17_0), U3.9 (D0)
XD1: U1.P127 (IO_L36P_GCLK15_0), U3.10 (D1)
XD2: U1.P124 (IO_L37P_GCLK13_0), U3.13 (D2)
XD3: U1.P123 (IO_L37N_GCLK12_0), U3.14 (D3)
XD4: U1.P115 (IO_L65P_SCP3_0), U3.31 (D4)
XD5: U1.P117 (IO_L64P_SCP5_0), U3.32 (D5)
XD6: U1.P119 (IO_L63P_SCP7_0), U3.35 (D6)
XD7: U1.P126 (IO_L36N_GCLK14_0), U3.36 (D7)

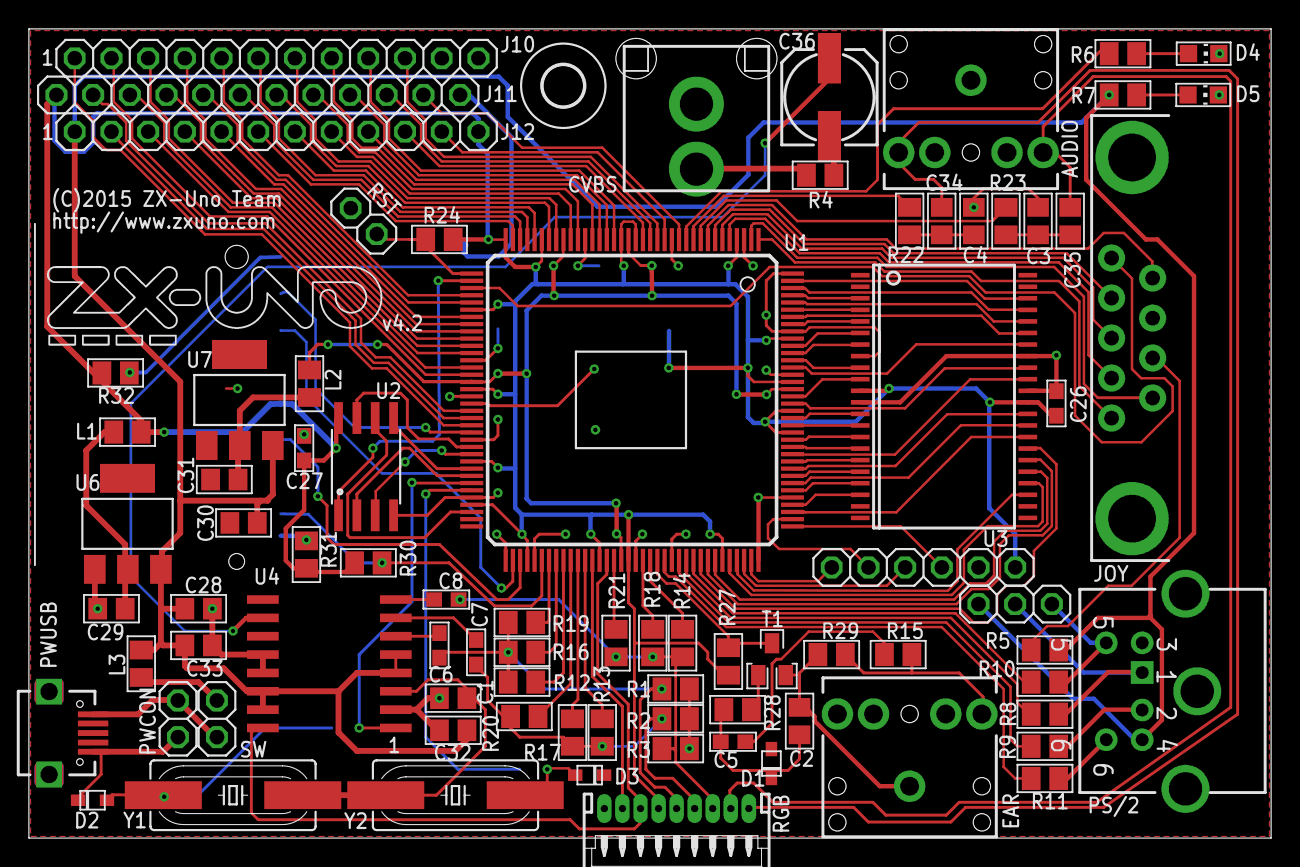
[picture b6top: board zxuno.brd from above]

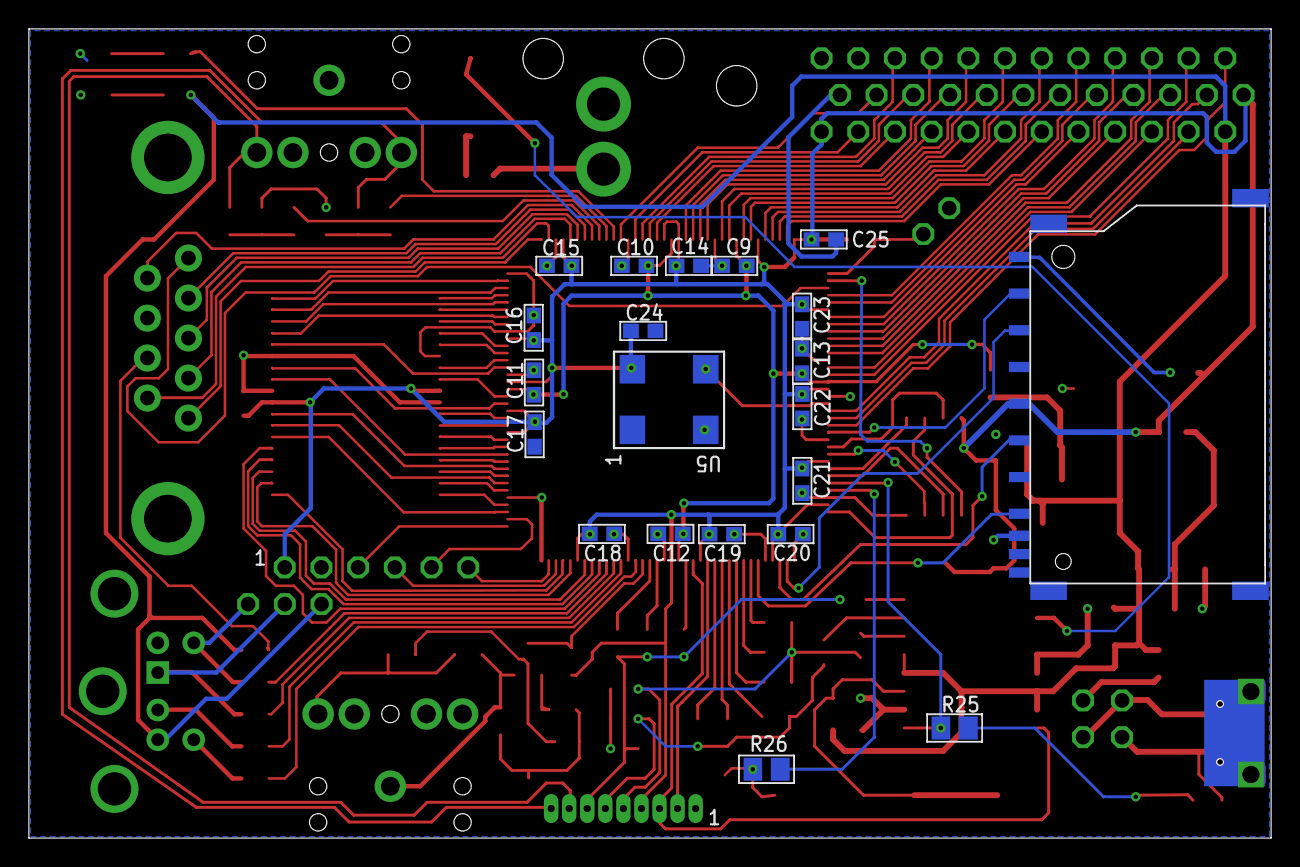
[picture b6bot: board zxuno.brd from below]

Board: 2 copper layers, 86.0 x 56.0 mm, 103 parts (21 on the bottom side), 141 nets.

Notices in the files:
hardware/addons_zxuno/z80.brd:
(C)2015 mcleod_ideafix
hardware/zxuno.brd:
(C)2015 ZX-Uno Team
parts and their libraries:
SparkFun-Connectors: Licensing: CC v3.0 Share-Alike You are welcome to use this library for commercial purposes.
diy-modules: Released under the Creative Commons Attribution 4.0 International License: http://creativecommons.org/licenses/by/4.0
74LV: Copyright (C) 2008, Bob Starr
